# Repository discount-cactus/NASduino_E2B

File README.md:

# NASduino (E2B)
NASduino is a simple Arduino-based NAS for enabling small-scale projects to access large amounts of data in a simple and scalable manner. This is made capable through my single-wire communications protocol E2B.

To access the Macchiato SSD board files: https://github.com/discount-cactus/macchiato-ssd

## Required materials
- 2 x ESP32's
- 1-12 x Macchiato SSD's
- 1 x Pushbutton
- Wires

## Wiring
# NAS
The default NAS setup uses two ESP32's (along with the SSD board I developed) used as a host and another as the NAS controller and communicate through ESP-NOW. This is the default setup but other ways are certainly possible with minor modification to this circuit setup.

- Host device: No additional hardware
- NAS Controller:
    - Button: Connected between pin 5 and GND (other pins work fine as long as the code is updated with the new pin value)
    - E2B line: Connected to pin 4 and Macchiato SSD's E2B pin (a 4.7k pullup resistor is required)
- Macchiato SSD:
    - E2B pin: Connected to E2B pin and pin 4 on NAS Controller device

# DAS
The DAS uses almost the same setup as the NAS wiring, with the absence of one ESP32 while the other one now assumes the role of the host and NAS controller.

- Host Device/NAS Controller:
    - Button: Connected between pin 5 and GND (other pins work fine as long as the code is updated with the new pin value)
    - E2B line: Connected to pin 4 and Macchiato SSD's E2B pin (a 4.7k pullup resistor is required)
- Macchiato SSD:
    - E2B pin: Connected to E2B pin and pin 4 on NAS Controller device

# Software Setup
1. For the Macchiato SSD board, flash the macchiato_ssd_eeprom example sketch to the on-board Arduino Nano.
2. For the Conrtoller ESP32, flash the nas_controller example sketch to the board.
   - If setup as a DAS, flash the das_simple_read_write example sketch to the board.
3. For the Client ESP32, flash the client_read_write_test example sketch to the board.

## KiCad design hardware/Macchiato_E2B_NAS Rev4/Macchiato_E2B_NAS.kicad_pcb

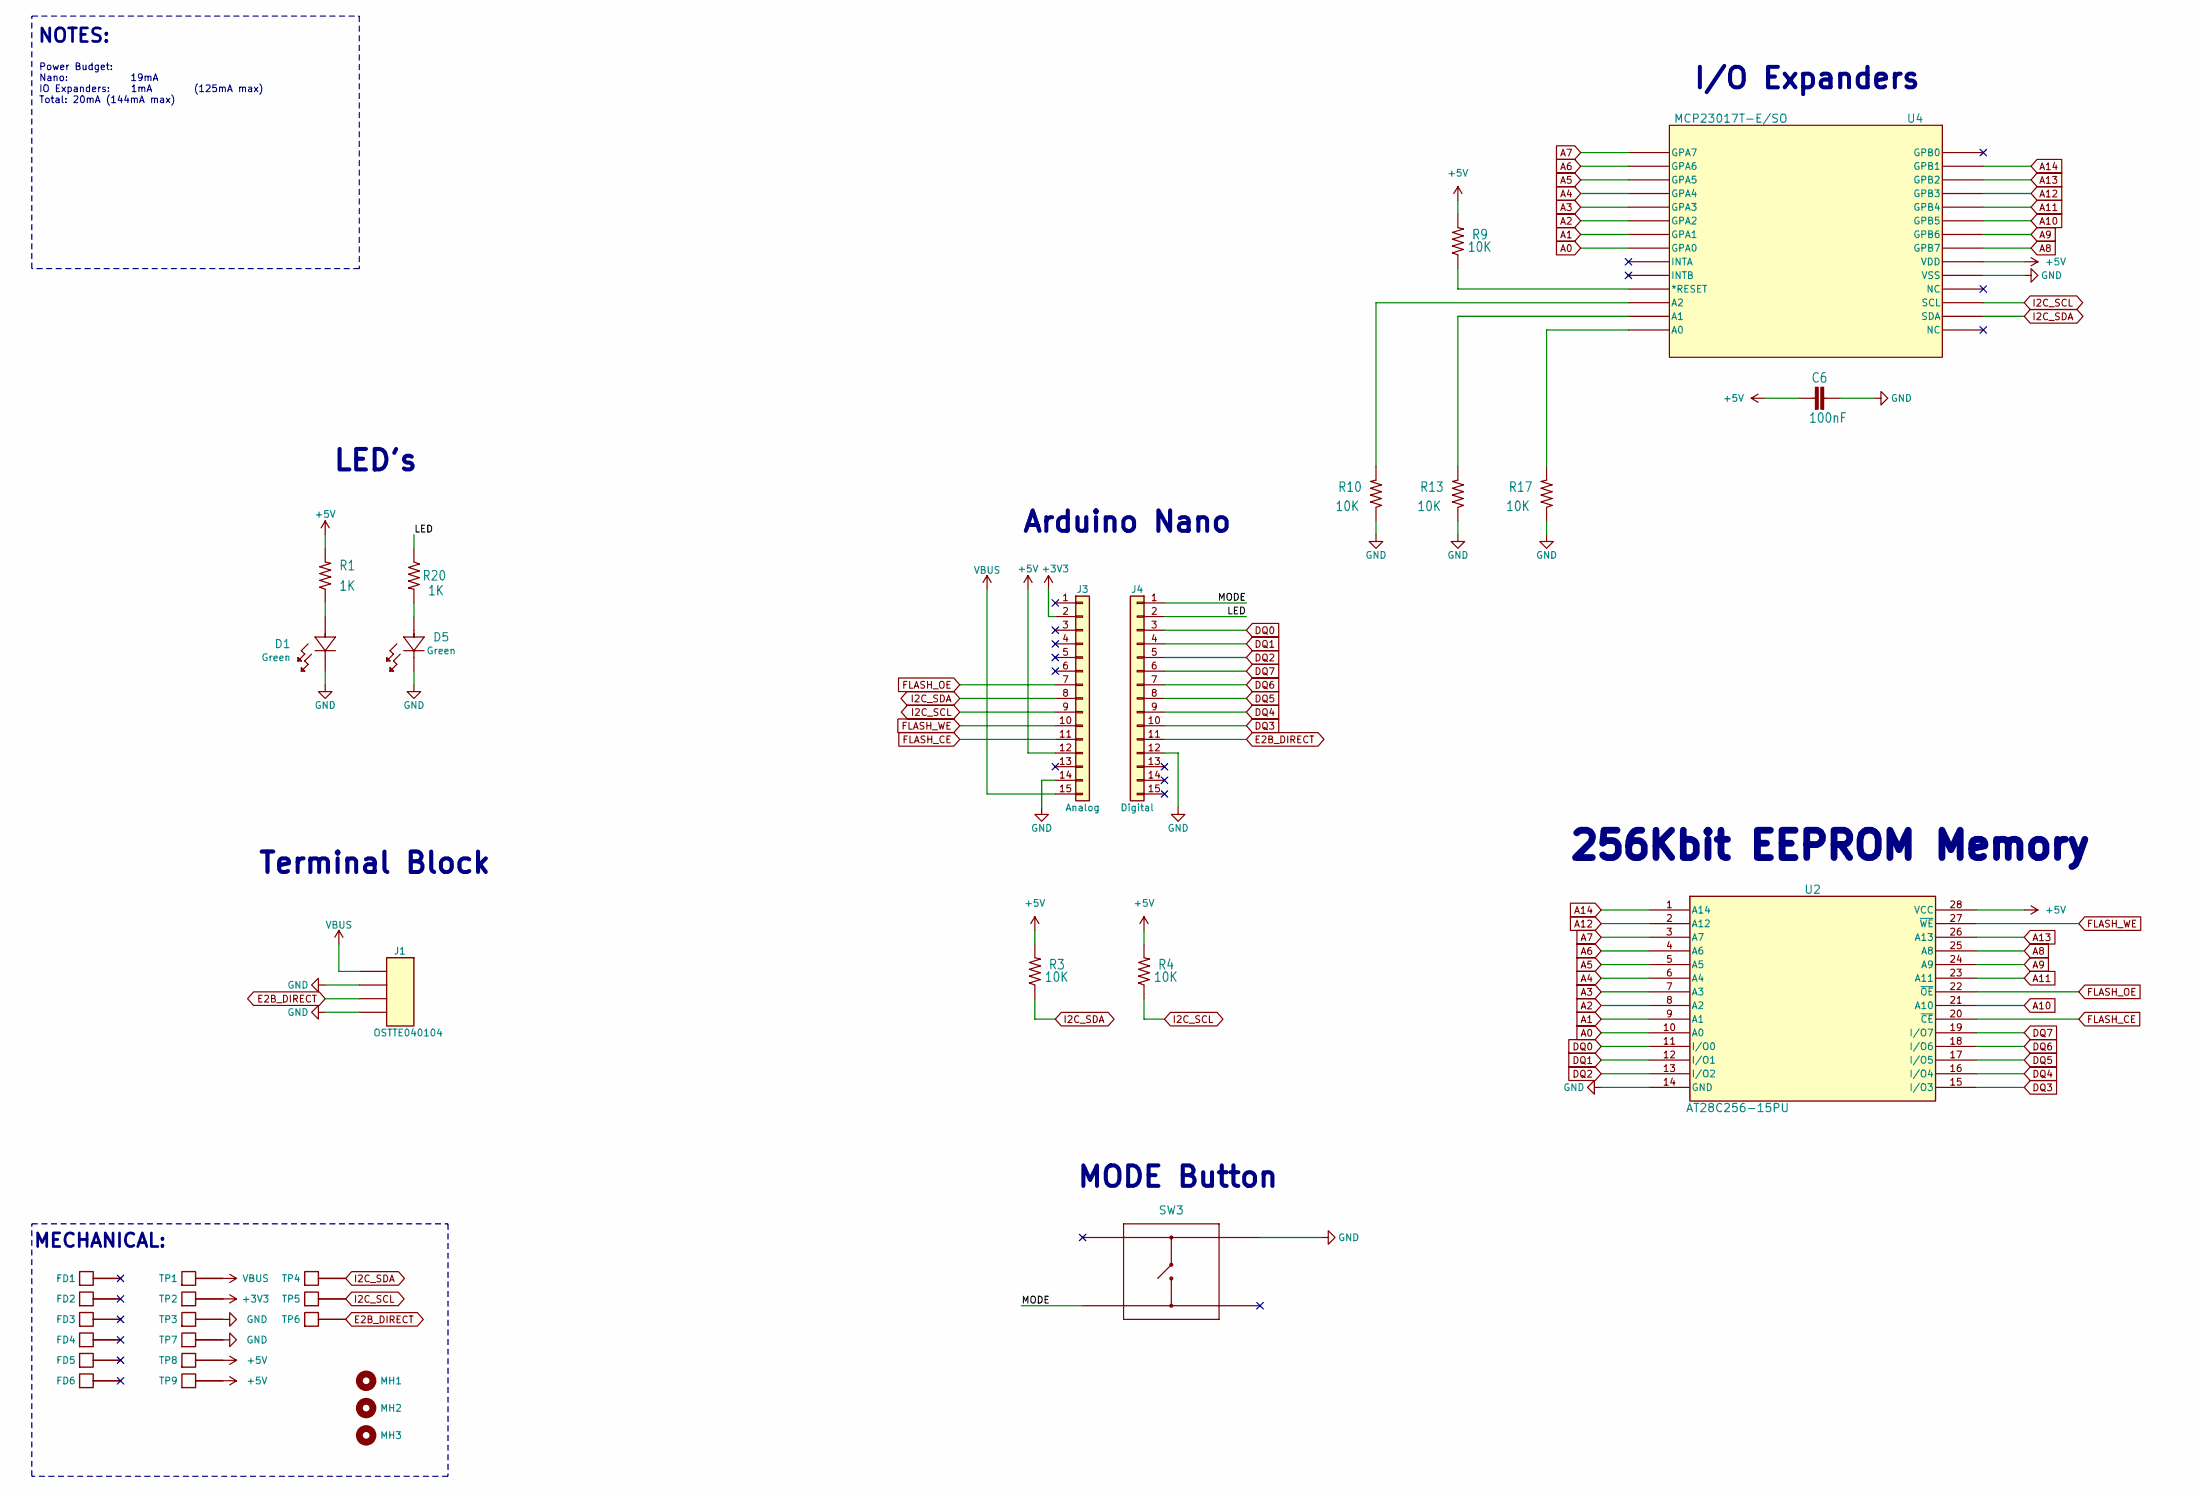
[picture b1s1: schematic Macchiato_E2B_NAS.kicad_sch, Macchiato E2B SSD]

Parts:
C6: 100nF; C_0603; Rating 50V; Part Number CL10B104KB8NNNC
D1, D5: LED_0603; Part Number LTST-C191KGKT
FD1, FD2, FD3, FD4, FD5, FD6: Fiducial_1.5mm_Mask3mm
J1: OSTTE040104; Rating 10A; Part Number OSTTE040104
J3: Analog; PinSocket_1x15_P2.54mm_Vertical
J4: Digital; PinSocket_1x15_P2.54mm_Vertical
MH1, MH2, MH3: MountingHole; MountingHole_3.2mm_M3
R1, R20: 1K; R_0603; Rating 1/10W; Part Number RMCF0603FT1K00
R3, R4, R9, R10, R13, R17: 10K; R_0603; Rating 1/10W; Part Number RMCF0603FT10K0
SW3: PTS815 SJM 250 SMTR LFS; Part Number PTS815SJM250SMTRLFS
TP1, TP2, TP3, TP4, TP5, TP6, TP7, TP8, TP9: TESTPOINT
U2: AT28C256-15PU; Part Number AT28C256-15PU
U4: MCP23017T-E/SO; MCP23017T-E_SO; Part Number MCP23017T-E/SO

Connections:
+3V3: J3.2, TP2.1
+5V: C6.1, J3.12, R1.2, R3.2, R4.2, R9.2, TP8.1, TP9.1, U2.28 (VCC), U4.9 (VDD)
/LED: J4.2, R20.1
/MODE: J4.1, SW3.3
A0: U2.10 (A0), U4.21 (GPA0)
A1: U2.9 (A1), U4.22 (GPA1)
A2: U2.8 (A2), U4.23 (GPA2)
A3: U2.7 (A3), U4.24 (GPA3)
A4: U2.6 (A4), U4.25 (GPA4)
A5: U2.5 (A5), U4.26 (GPA5)
A6: U2.4 (A6), U4.27 (GPA6)
A7: U2.3 (A7), U4.28 (GPA7)
A8: U2.25 (A8), U4.8 (GPB7)
A9: U2.24 (A9), U4.7 (GPB6)
A10: U2.21 (A10), U4.6 (GPB5)
A11: U2.23 (A11), U4.5 (GPB4)
A12: U2.2 (A12), U4.4 (GPB3)
A13: U2.26 (A13), U4.3 (GPB2)
A14: U2.1 (A14), U4.2 (GPB1)
DQ0: J4.3, U2.11 (I/O0)
DQ1: J4.4, U2.12 (I/O1)
DQ2: J4.5, U2.13 (I/O2)
DQ3: J4.10, U2.15 (I/O3)
DQ4: J4.9, U2.16 (I/O4)
DQ5: J4.8, U2.17 (I/O5)
DQ6: J4.7, U2.18 (I/O6)
DQ7: J4.6, U2.19 (I/O7)
E2B_DIRECT: J1.3, J4.11, TP6.1
FLASH_CE: J3.11, U2.20 (~CE)
FLASH_OE: J3.7, U2.22 (~OE)
FLASH_WE: J3.10, U2.27 (~WE)
GND: C6.2, D1.1, D5.1, J1.2, J1.4, J3.14, J4.12, R10.1, R13.1, R17.1, SW3.2, TP3.1, TP7.1, U2.14 (GND), U4.10 (VSS)
I2C_SCL: J3.9, R4.1, TP5.1, U4.12 (SCL)
I2C_SDA: J3.8, R3.1, TP4.1, U4.13 (SDA)
unnamed: D1.2, R1.1
unnamed: D5.2, R20.2
unnamed: R9.1, U4.18 (*RESET)
unnamed: R17.2, U4.15 (A0)
unnamed: R13.2, U4.16 (A1)
unnamed: R10.2, U4.17 (A2)
VBUS: J1.1, J3.15, TP1.1

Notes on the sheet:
LED's
MECHANICAL:
Terminal Block
MODE Button
Power Budget: Nano: 19mA IO Expanders: 1mA (125mA max) Total: 20mA (144mA max)
256Kbit EEPROM Memory
Arduino Nano
I/O Expanders
NOTES:

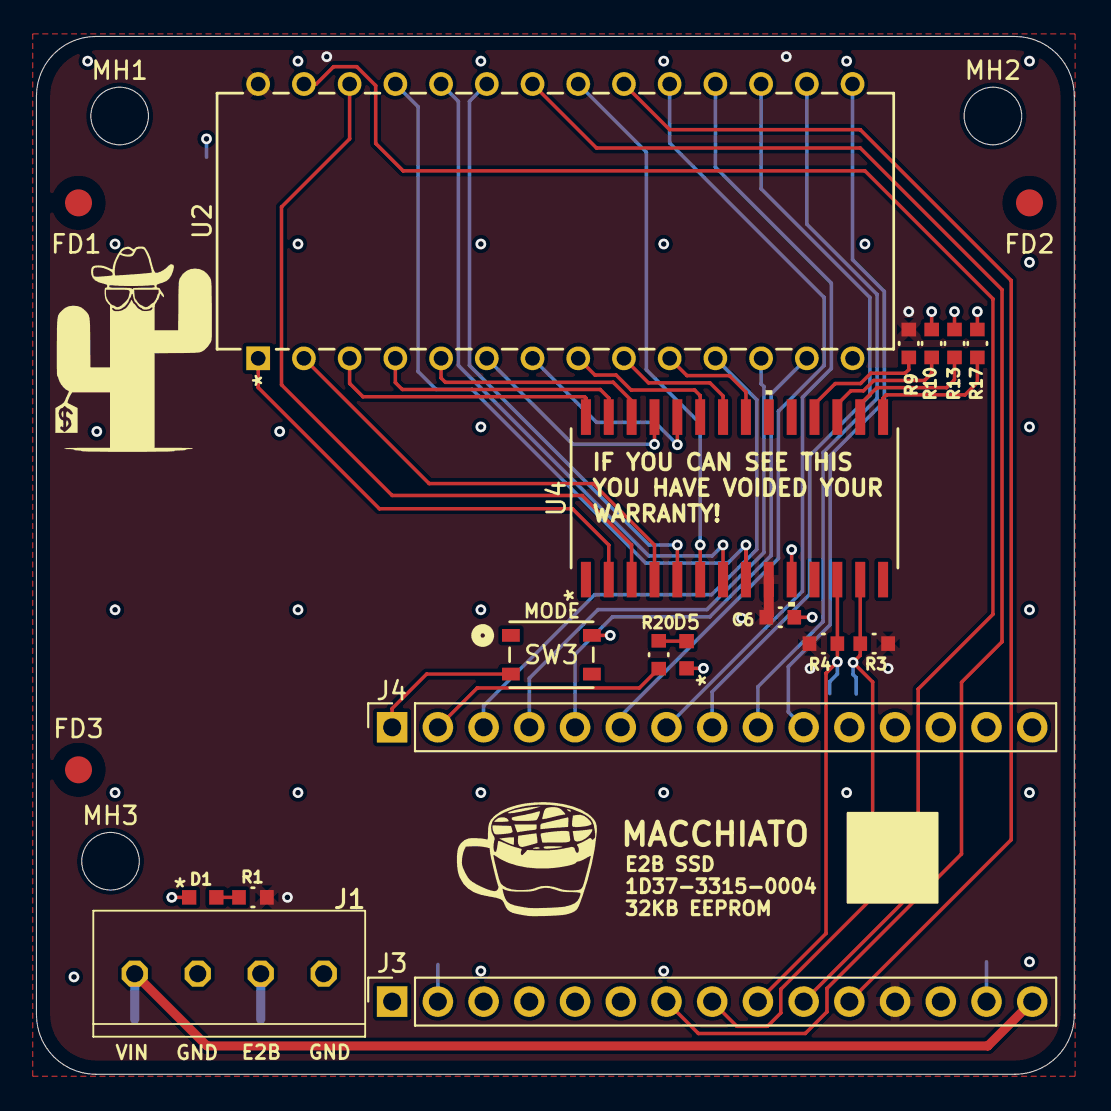
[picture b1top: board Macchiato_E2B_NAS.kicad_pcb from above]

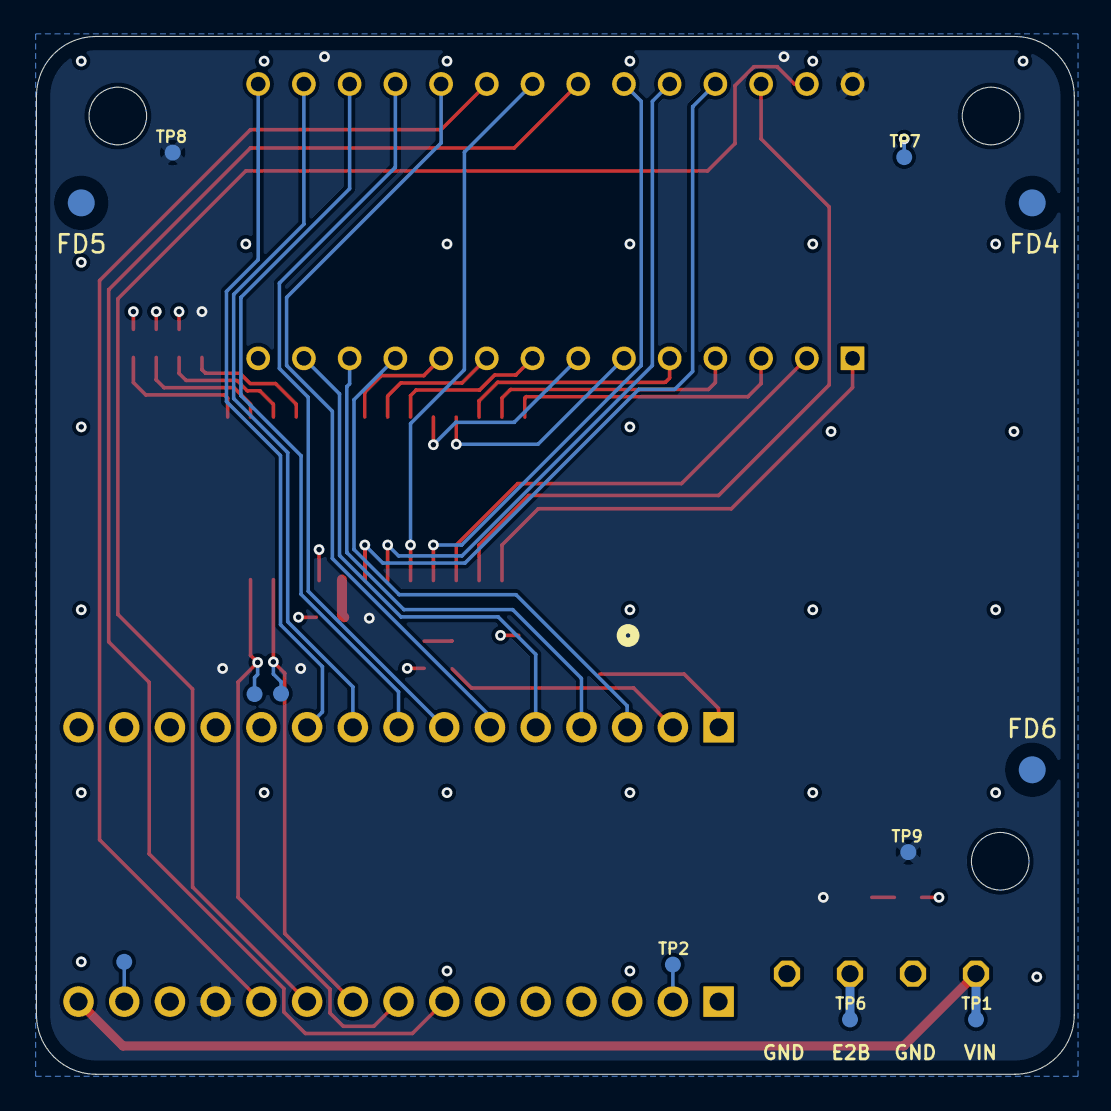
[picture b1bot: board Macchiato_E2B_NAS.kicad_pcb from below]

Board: 4 copper layers, 57.7 x 57.7 mm, 35 parts (12 on the bottom side), 41 nets.

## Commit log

2025-03-01 Initial files commit
2025-03-02 NAS Controller sends read data to Host
    During a read command from a host device to the E2B NAS, the Controller Device can now transmit the data read from an SSD back to the Host device through the Controller device.
2025-03-10 Updated example sketches per testing
2025-03-17 Updated example files per testing
2025-03-25 Updated sketches from testing
2025-03-28 Many improvements per testing
    Last major push before moving into an integrated test.
2025-08-18 Updated files per testing with Macchiato Rev4
2025-08-20 Changes for stable reading and writing 8-bit data
    Verified with successful client-to-SSD test at 0.5s intervals.
2025-08-20 Removed unused files
2025-08-21 Added simple read and write test sketch
2025-08-23 Updated file names
2025-08-24 Minor library improvements
2025-08-24 Repository restructure to include PCB's
2025-08-24 Repo restructuring
2025-08-24 Updated nas_controller code
2025-08-26 Initial macchiato_ssd_sram example
2025-08-27 macchiato_ssd_sram supports word- and byte- sized reads and writes
2025-09-13 Bug fix in SRAM example sketch
2025-09-24 Improvements for supporting word and byte W/R
2025-09-26 Minor code improvements
2025-10-05 Initial Marlin UI integration commit
2025-10-05 Added Marlin UI file to library
2025-11-07 Added marlin_icon.png to python folder
2025-11-08 Added functionality for speed tests
2025-11-08 Example sketch cleanup
2025-11-08 Updated GUI to support displaying time metrics
2025-11-08 Added more SSD decoding in run_diagnostics()
2025-11-08 Minor controller-to-Python improvements
2025-11-09 Converted reading and writing to functions + Added ping_connected_devices()
2025-11-13 Initial commit for sending client data to controller
2025-11-13 Improved client info packet structure
2025-11-13 Improvements to NAS controller handling client data
2025-11-13 NAS controller sends client data with packet in run_diagnostics()
2025-11-14 Marlin UI decodes diagnostics data and updates graphs accordingly
2025-11-14 Added virtual power budget calculation functionality
